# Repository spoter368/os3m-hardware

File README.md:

# os3m-hardware

This repo is a fork of the already existing os3m-hardware repo for the HEIA-FR University
* Original Repo : https://github.com/spoter368/os3m-software

## HEIA-FR
All the HEIA-FR specific model for 3D Printing can be found in the HEIA folder.

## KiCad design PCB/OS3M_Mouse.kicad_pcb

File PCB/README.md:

# OS3M Mouse PCB

Here are all the files pertaining to the OS3M mouse's PCB. I only commit and push here when I have a full revision update to the PCB. So far there are only 2 revisions, 0 and 1, and you should only make the current one (1). Gerbers can be found in the os3m-gerbers folder, and can be sent to JLC for easy fab. I also plan on selling these on tindie at some point.

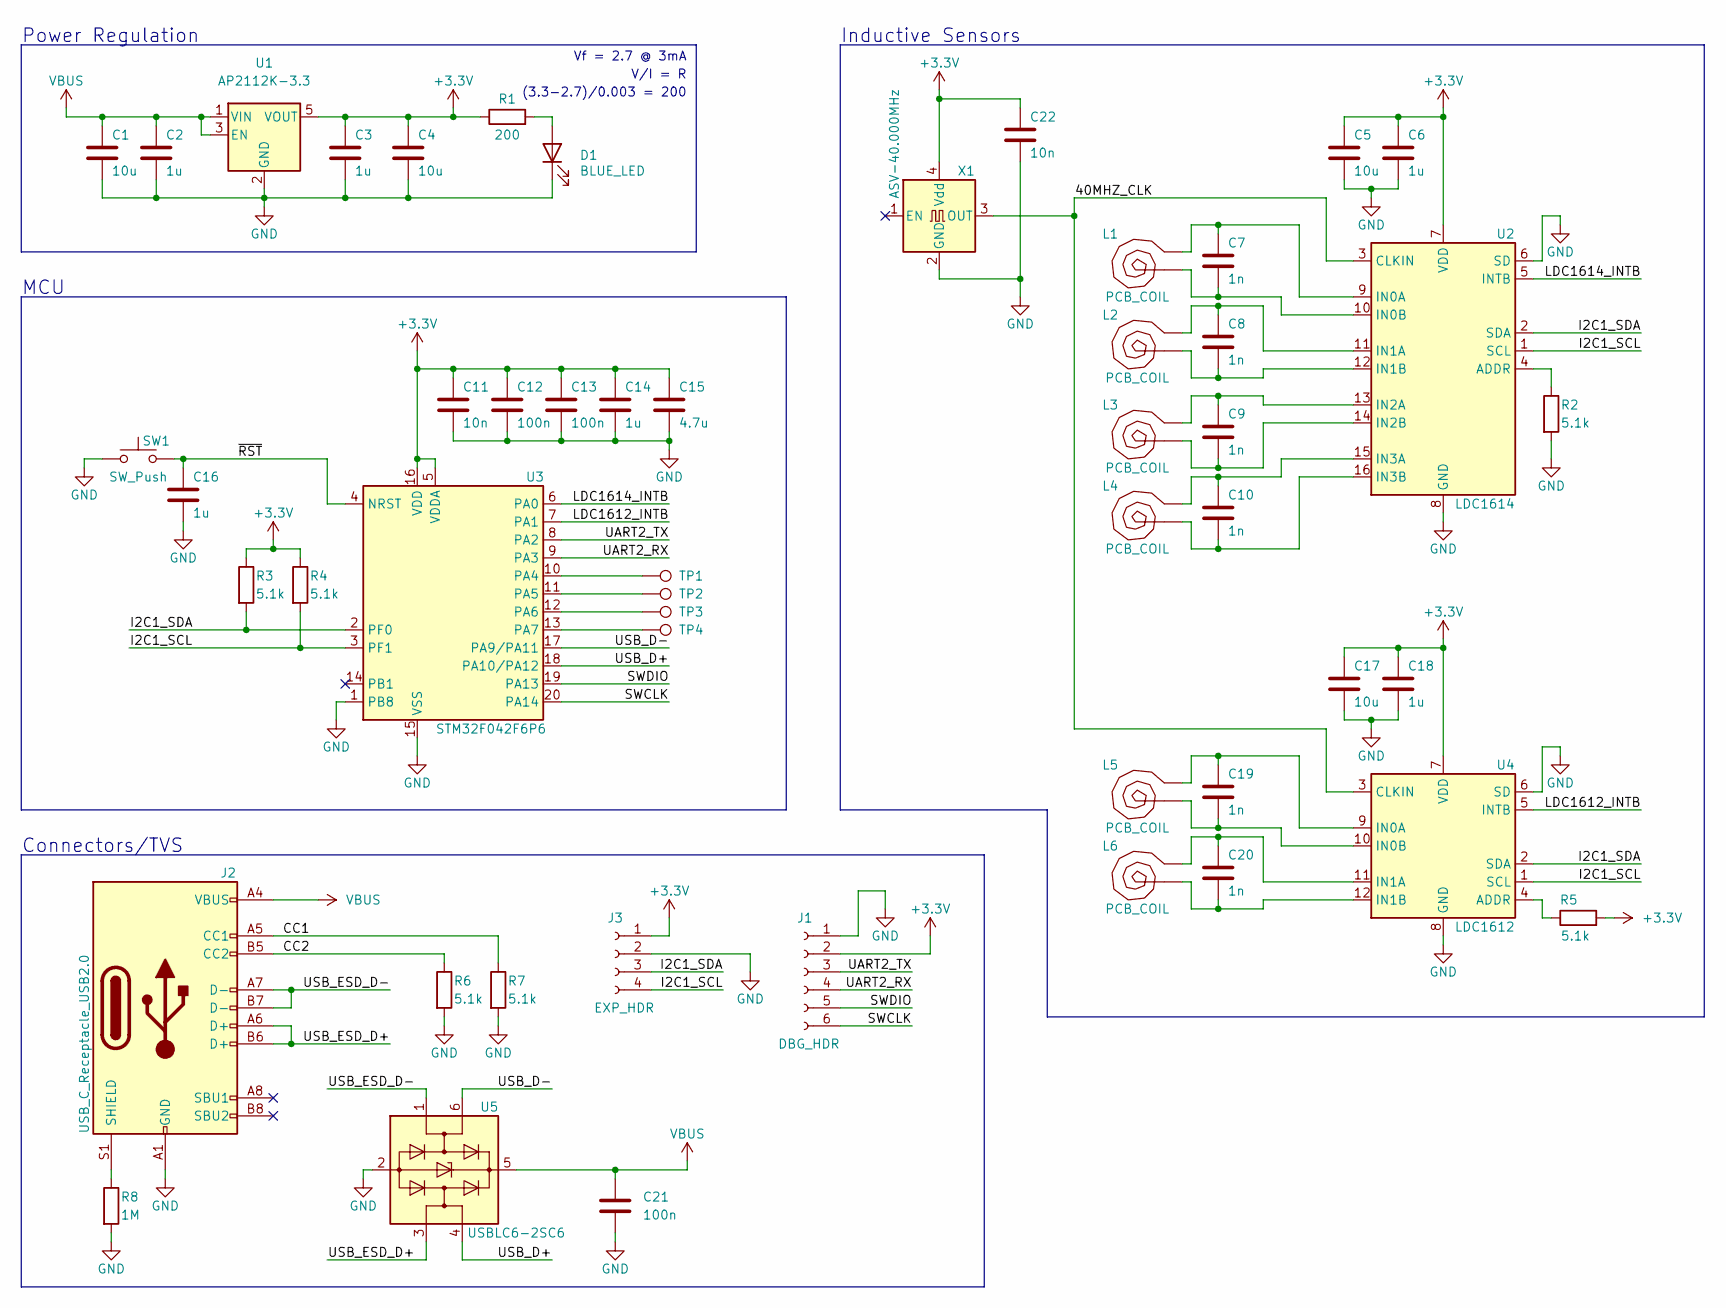
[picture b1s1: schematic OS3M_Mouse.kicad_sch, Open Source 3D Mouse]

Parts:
C1, C4, C5, C17: 10u; C_0402_1005Metric
C2, C3, C6, C14, C16, C18: 1u; C_0402_1005Metric
C7, C8, C9, C10, C19, C20: 1n; C_0402_1005Metric
C11, C22: 10n; C_0402_1005Metric
C12, C13, C21: 100n; C_0402_1005Metric
C15: 4.7u; C_0402_1005Metric
D1: BLUE_LED; LED_0603_1608Metric
J1: DBG_HDR; PinHeader_1x06_P2.54mm_Vertical
J2: USB_C_Receptacle_USB2.0; USB_C_Receptacle_XKB_U262-16XN-4BVC11
J3: EXP_HDR; PinSocket_2x02_P2.54mm_Horizontal
L1, L2, L3, L4, L5, L6: PCB_COIL; COIL_GENERATOR_0
R1: 200; R_0603_1608Metric
R2, R3, R4, R5, R6, R7: 5.1k; R_0402_1005Metric
R8: 1M; R_0402_1005Metric
SW1: SW_Push; SW_SPST_TL3305A
TP1, TP2, TP3, TP4: TestPoint; TestPoint_Pad_D2.0mm
U1: AP2112K-3.3; SOT-23-5
U2: LDC1614; WQFN-16-1EP_4x4mm_P0.5mm_EP2.6x2.6mm_ThermalVias
U3: STM32F042F6P6; TSSOP-20_4.4x6.5mm_P0.65mm
U4: LDC1612; WSON-12-1EP_4x4mm_P0.5mm_EP2.6x3mm_ThermalVias
U5: USBLC6-2SC6; SOT-23-6
X1: ASV-40.000MHz; Oscillator_SMD_Abracon_ASV-4Pin_7.0x5.1mm

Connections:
+3.3V: C3.1, C4.1, C5.1, C6.1, C11.1, C12.1, C13.1, C14.1, C15.1, C17.1, C18.1, C22.1, J1.2, J3.1, R1.1, R3.1, R4.1, R5.2, U1.5 (VOUT), U2.7 (VDD), U3.5 (VDDA), U3.16 (VDD), U4.7 (VDD), X1.4 (Vdd)
/40MHZ_CLK: U2.3 (CLKIN), U4.3 (CLKIN), X1.3 (OUT)
/CC1: J2.A5 (CC1), R7.1
/CC2: J2.B5 (CC2), R6.1
/I2C1_SCL: J3.4, R4.2, U2.1 (SCL), U3.3 (PF1), U4.1 (SCL)
/I2C1_SDA: J3.3, R3.2, U2.2 (SDA), U3.2 (PF0), U4.2 (SDA)
/LDC1612_INTB: U3.7 (PA1), U4.5 (INTB)
/LDC1614_INTB: U2.5 (INTB), U3.6 (PA0)
/SWCLK: J1.6, U3.20 (PA14)
/SWDIO: J1.5, U3.19 (PA13)
/UART2_RX: J1.4, U3.9 (PA3)
/UART2_TX: J1.3, U3.8 (PA2)
/USB_D+: U3.18 (PA10/PA12), U5.4 (I/O2)
/USB_D-: U3.17 (PA9/PA11), U5.6 (I/O1)
/USB_ESD_D+: J2.A6 (D+), J2.B6 (D+), U5.3 (I/O2)
/USB_ESD_D-: J2.A7 (D-), J2.B7 (D-), U5.1 (I/O1)
/~RST: C16.1, SW1.2, U3.4 (NRST)
GND: C1.2, C2.2, C3.2, C4.2, C5.2, C6.2, C11.2, C12.2, C13.2, C14.2, C15.2, C16.2, C17.2, C18.2, C21.2, C22.2, D1.1 (K), J1.1, J2.A1 (GND), J2.A12 (GND), J2.B1 (GND), J2.B12 (GND), J3.2, R2.2, R6.2, R7.2, R8.2, SW1.1, U1.2 (GND), U2.6 (SD), U2.8 (GND), U2.17 (GND), U3.1 (PB8), U3.15 (VSS), U4.6 (SD), U4.8 (GND), U4.13 (GND), U5.2 (GND), X1.2 (GND)
unnamed: C7.1, L1.1, U2.9 (IN0A)
unnamed: C7.2, L1.2, U2.10 (IN0B)
unnamed: C8.1, L2.1, U2.11 (IN1A)
unnamed: C8.2, L2.2, U2.12 (IN1B)
unnamed: C9.1, L3.1, U2.13 (IN2A)
unnamed: C9.2, L3.2, U2.14 (IN2B)
unnamed: C10.1, L4.1, U2.15 (IN3A)
unnamed: C10.2, L4.2, U2.16 (IN3B)
unnamed: C19.1, L5.1, U4.9 (IN0A)
unnamed: C19.2, L5.2, U4.10 (IN0B)
unnamed: C20.1, L6.1, U4.11 (IN1A)
unnamed: C20.2, L6.2, U4.12 (IN1B)
unnamed: D1.2 (A), R1.2
unnamed: J2.S1 (SHIELD), R8.1
unnamed: R2.1, U2.4 (ADDR)
unnamed: R5.1, U4.4 (ADDR)
unnamed: TP1.1, U3.10 (PA4)
unnamed: TP2.1, U3.11 (PA5)
unnamed: TP3.1, U3.12 (PA6)
unnamed: TP4.1, U3.13 (PA7)
VBUS: C1.1, C2.1, C21.1, J2.A4 (VBUS), J2.A9 (VBUS), J2.B4 (VBUS), J2.B9 (VBUS), U1.1 (VIN), U1.3 (EN), U5.5 (VBUS)

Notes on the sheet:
Inductive Sensors
MCU
Power Regulation
(3.3-2.7)/0.003 = 200
V/I = R
Connectors/TVS
Vf = 2.7 @ 3mA

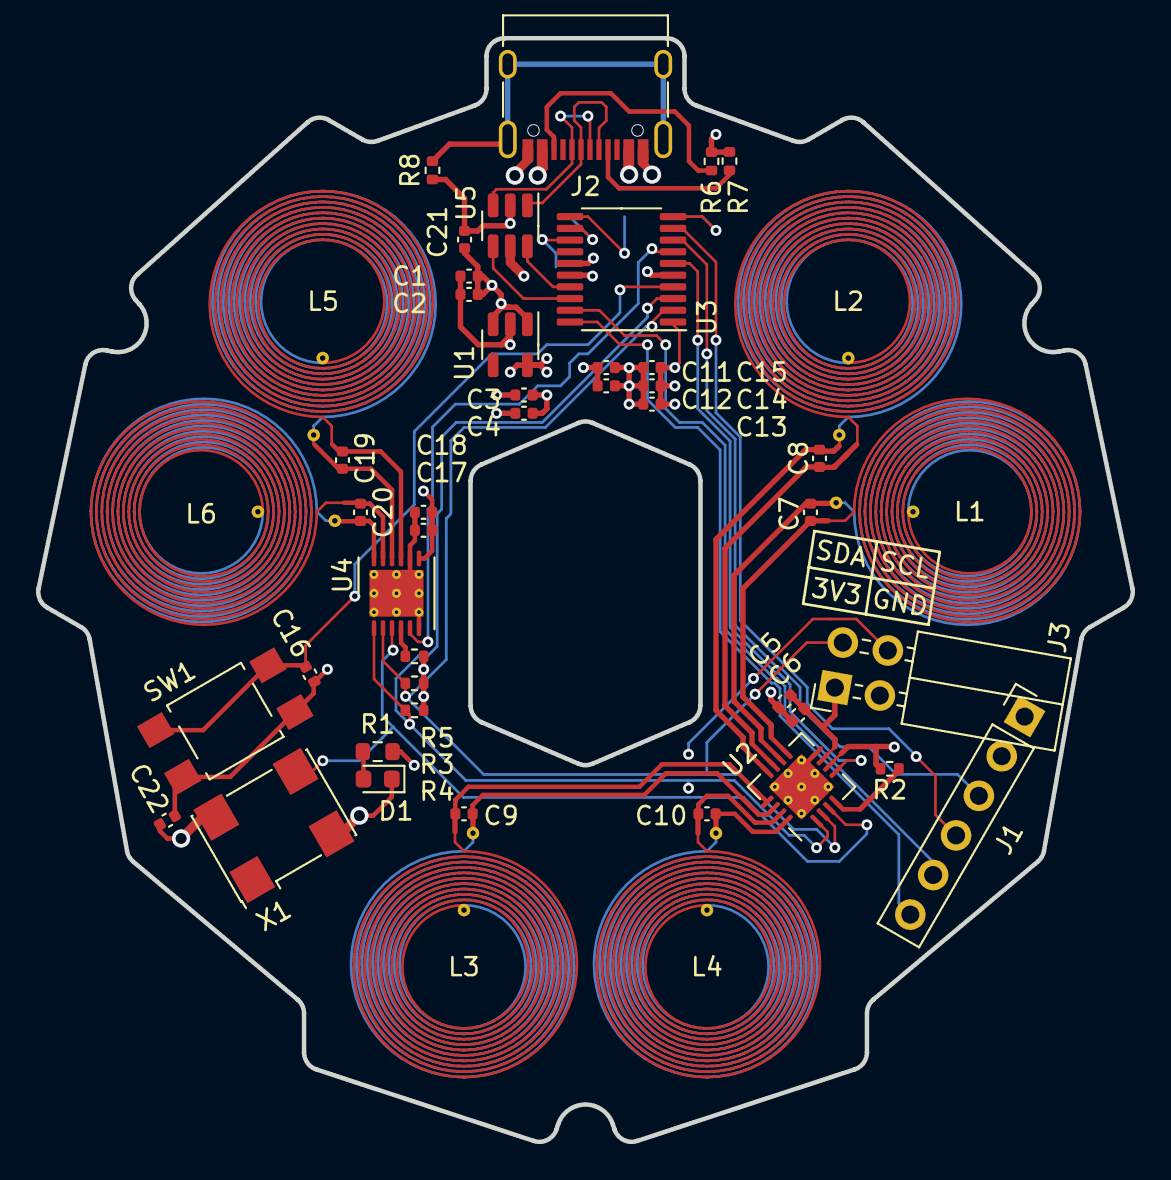
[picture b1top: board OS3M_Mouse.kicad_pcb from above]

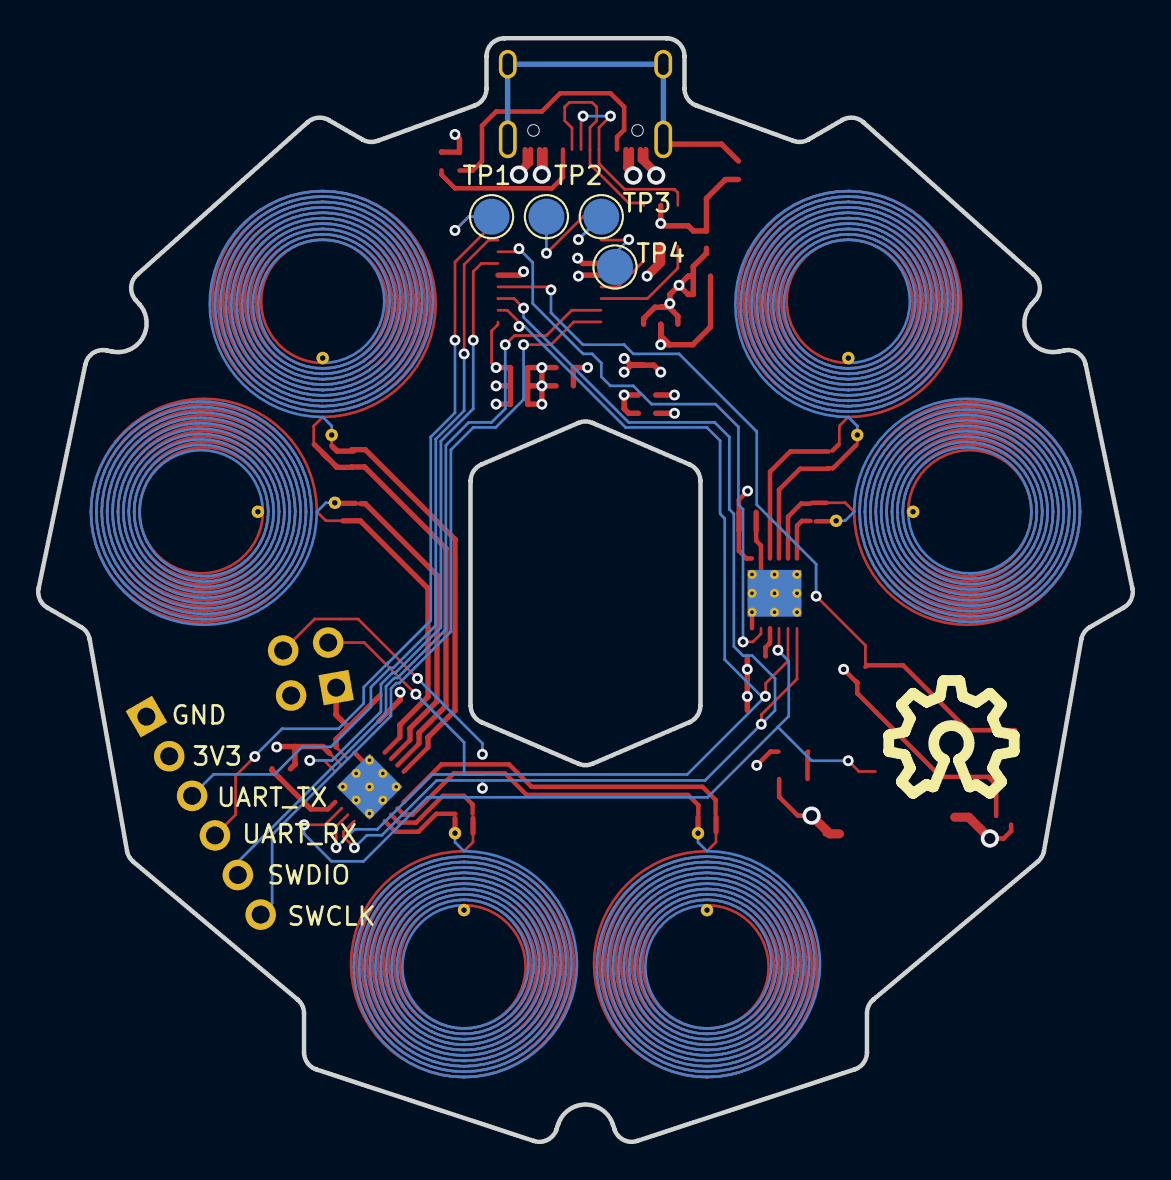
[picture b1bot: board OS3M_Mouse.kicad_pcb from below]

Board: 4 copper layers, 60.8 x 61.3 mm, 51 parts (4 on the bottom side), 39 nets.

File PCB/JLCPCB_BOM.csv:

Comment,Designator,Footprint,JLCPCB Part#,Quantity
10u,"C1, C4, C5, C17",Capacitor_SMD:C_0402_1005Metric,C15525,4
1u,"C2, C3, C6, C14, C16, C18",Capacitor_SMD:C_0402_1005Metric,C52923,6
1n,"C7, C8, C9, C10, C19, C20",Capacitor_SMD:C_0402_1005Metric,C126493,6
10n,"C11, C22",Capacitor_SMD:C_0402_1005Metric,C15195,2
100n,"C12, C13, C21",Capacitor_SMD:C_0402_1005Metric,C1525,3
4.7u,C15,Capacitor_SMD:C_0402_1005Metric,C23733,1
BLUE_LED,D1,LED_SMD:LED_0603_1608Metric,C389520,1
200,R1,Resistor_SMD:R_0603_1608Metric,C22962,1
5.1k,"R2, R3, R4, R5, R6, R7",Resistor_SMD:R_0402_1005Metric,C25905,6
1M,R8,Resistor_SMD:R_0402_1005Metric,C26083,1
SW_Push,SW1,Button_Switch_SMD:SW_SPST_TL3305A,C2886899,1
AP2112K-3.3,U1,Package_TO_SOT_SMD:SOT-23-5,C51118,1
LDC1614,U2,Package_DFN_QFN:WQFN-16-1EP_4x4mm_P0.5mm_EP2.6x2.6mm_ThermalVias,C968448,1
STM32F042F6P6,U3,Package_SO:TSSOP-20_4.4x6.5mm_P0.65mm,C2969989,1
LDC1612,U4,Package_SON:WSON-12-1EP_4x4mm_P0.5mm_EP2.6x3mm_ThermalVias,C1847959,1
USBLC6-2SC6,U5,Package_TO_SOT_SMD:SOT-23-6,C2687116,1
USB_C_Receptacle_USB2.0,J2,Connector_USB:USB_C_Receptacle_XKB_U262-16XN-4BVC11,C319148,1
XTAL_40MHz,X1,Oscillator:Oscillator_SMD_Abracon_ASV-4Pin_7.0x5.1mm,C24796 ,1

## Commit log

2023-11-21 add step and 3mf files
2023-12-10 Swapped inner layers to get GND plane close to components, fixed shorted UART
2023-12-10 Moved test points
2023-12-10 Renforced flexture and base extension
2023-12-11 Added BOM Files
2023-12-20 Fix shorted UART
2023-12-30 preliminary pass at wrist rest, fix base mounting points
2023-12-30 Update gitignore to ignore my test block
2024-01-13 Update to Rev2, JLC manufacturable
2024-02-08 Redesign of KnobHollow
    Modified the KnobHollow part to integrate the custom target theorized by lpurdy01
    https://github.com/lpurdy01/os3m_target_testing/blob/main/README.md
2024-02-12 CustomTarget integration in existing system
    -Changed KnobHollow to had support for the custom target theorized by lpurdy01 https://github.com/lpurdy01/os3m_target_testing/blob/main/README.md
    -Changed Stem to decrease the height of the CustomTarget from the PCB.
    -Changed Base to have a better interface with the Stem
2024-06-14 HEIA Rework
2024-06-23 Replace switch and oscillator for #19
